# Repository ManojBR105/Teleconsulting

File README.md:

# Teleconsulting
project demo video available at https://drive.google.com/file/d/1hCcPtmlnuc-eiRi7AZsOfsH53jTqFW1P/view?usp=sharing

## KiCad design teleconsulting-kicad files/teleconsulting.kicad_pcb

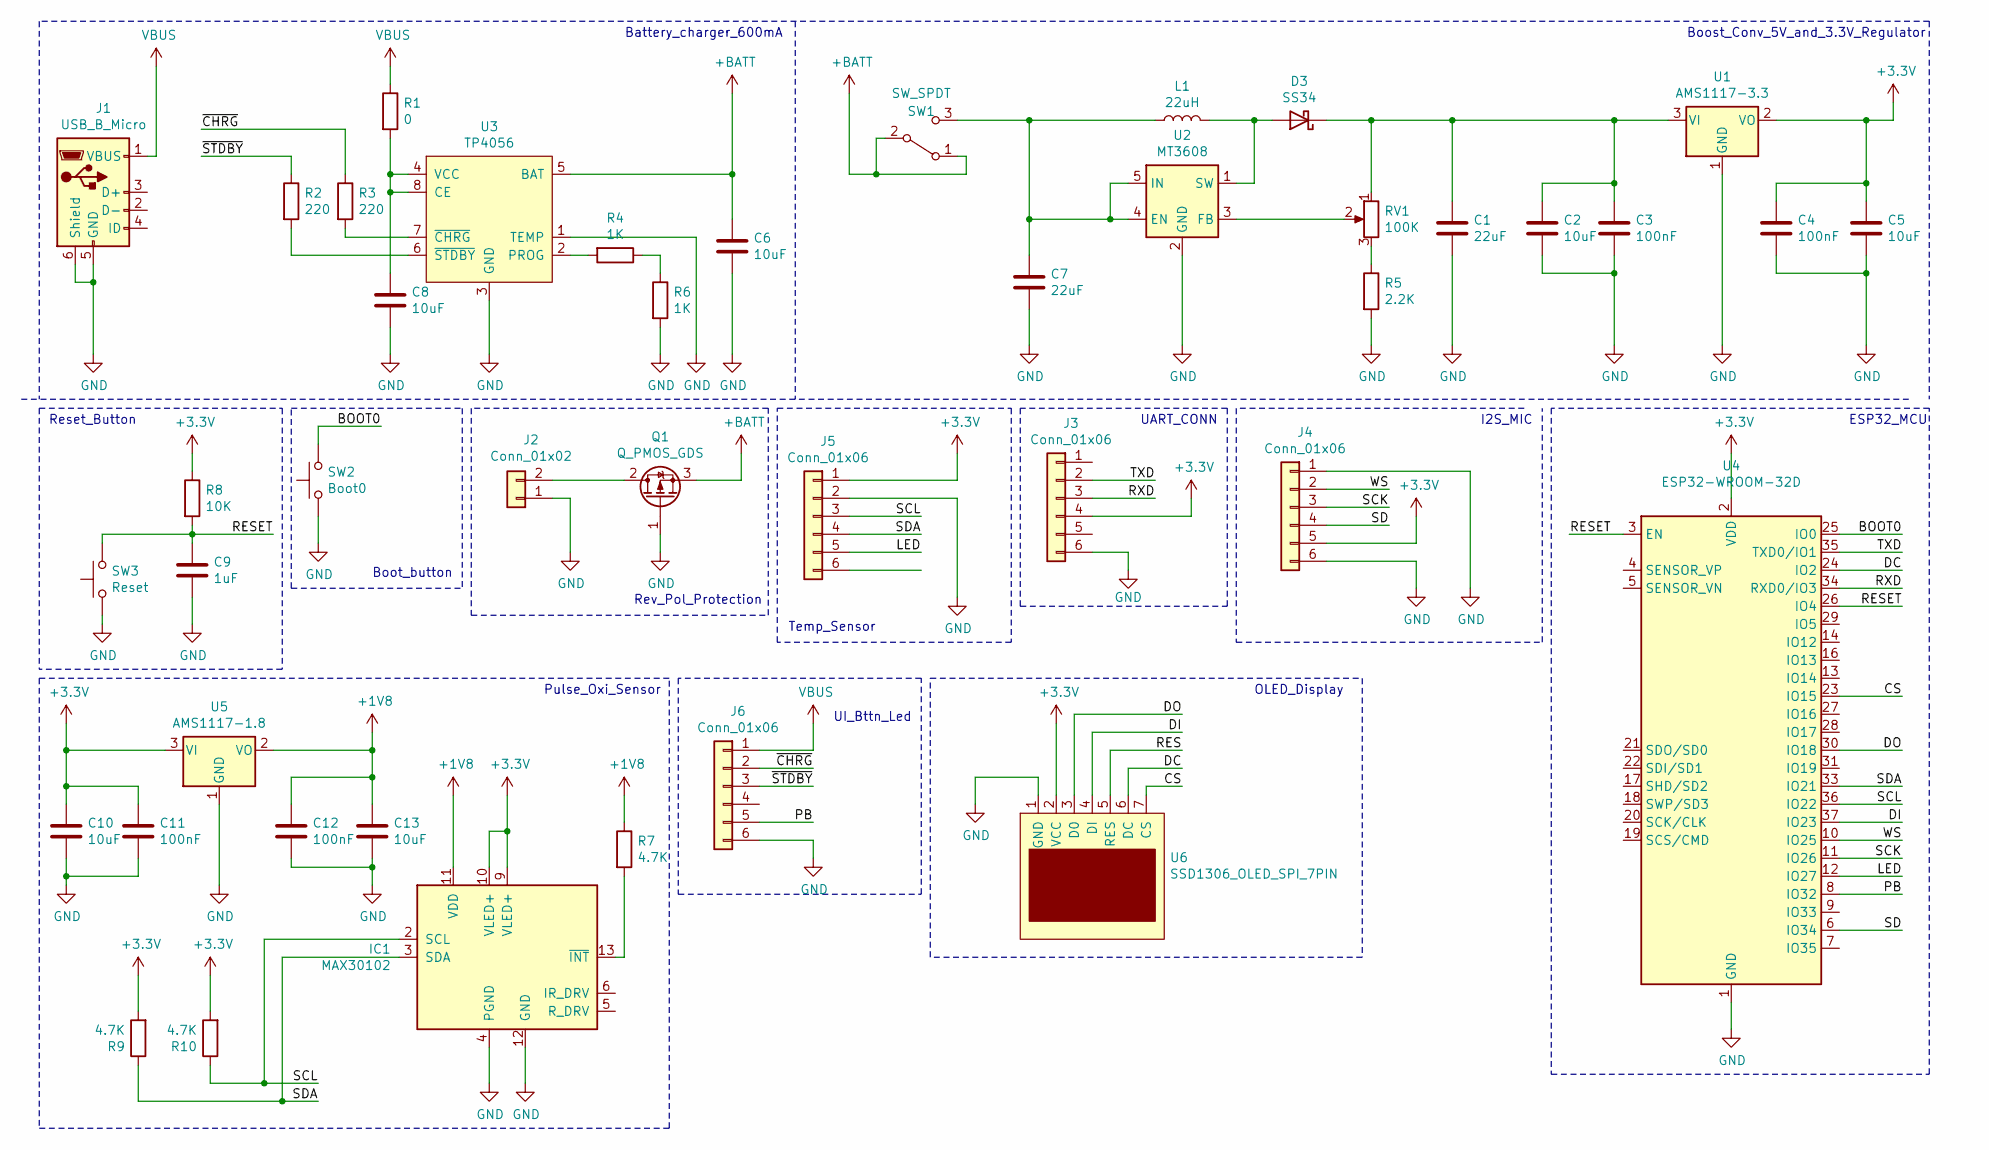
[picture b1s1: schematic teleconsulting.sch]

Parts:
C1, C7: 22uF; C_0805_2012Metric_Pad1.15x1.40mm_HandSolder
C2, C5, C10, C13: 10uF; C_0603_1608Metric_Pad1.05x0.95mm_HandSolder
C3, C4, C11, C12: 100nF; C_0603_1608Metric_Pad1.05x0.95mm_HandSolder
C6, C8: 10uF; C_0805_2012Metric_Pad1.15x1.40mm_HandSolder
C9: 1uF; C_0603_1608Metric_Pad1.05x0.95mm_HandSolder
D3: SS34; D_1812_4532Metric
IC1: MAX30102; Maxim_OLGA-14_3.3x5.6mm_P0.8mm
J1: USB_B_Micro; USB_Micro-B_Amphenol_10104110_Horizontal
J2: Conn_01x02; JST_EH_B2B-EH-A_1x02_P2.50mm_Vertical
J3, J4, J5, J6: Conn_01x06; JST_EH_B6B-EH-A_1x06_P2.50mm_Vertical
L1: 22uH; L_Taiyo-Yuden_NR-10050_9.8x10.0mm
Q1: Q_PMOS_GDS; SOT-23_Handsoldering
R1: 0; R_0805_2012Metric_Pad1.15x1.40mm_HandSolder
R2, R3: 220; R_0805_2012Metric_Pad1.15x1.40mm_HandSolder
R4, R6: 1K; R_0805_2012Metric_Pad1.15x1.40mm_HandSolder
R5: 2.2K; R_0603_1608Metric_Pad1.05x0.95mm_HandSolder
R7, R9, R10: 4.7K; R_0805_2012Metric_Pad1.15x1.40mm_HandSolder
R8: 10K; R_0603_1608Metric_Pad1.05x0.95mm_HandSolder
RV1: 100K; Potentiometer_Bourns_TC33X_Vertical
SW1: SW_SPDT; SW_CuK_OS102011MA1QN1_SPDT_Angled
SW2: Boot0; SW_Push_SPST_NO_Alps_SKRK
SW3: Reset; SW_Push_SPST_NO_Alps_SKRK
U1: AMS1117-3.3; SOT-223-3_TabPin2
U2: MT3608; SOT-23-6_Handsoldering
U3: TP4056; SOIC-8_3.9x4.9mm_P1.27mm
U4: ESP32-WROOM-32D; ESP32-WROOM-32
U5: AMS1117-1.8; SOT-223-3_TabPin2
U6: SSD1306_OLED_SPI_7PIN; ssd1306_oled_spi_7pin

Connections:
+1V8: C12.1, C13.1, IC1.11 (VDD), R7.1, U5.2 (VO)
+3V3: C4.1, C5.1, C10.1, C11.1, IC1.9 (VLED+), IC1.10 (VLED+), J3.4, J4.5, J5.1, R8.1, R9.2, R10.2, U1.2 (VO), U4.2 (VDD), U5.3 (VI), U6.2 (VCC)
+BATT: C6.1, Q1.3 (S), SW1.1 (A), SW1.2 (B), U3.5 (BAT)
/BOOT0: SW2.2, U4.25 (IO0)
/CS: U4.23 (IO15), U6.7 (CS)
/DC: U4.24 (IO2), U6.6 (DC)
/DI: U4.37 (IO23), U6.4 (DI)
/DO: U4.30 (IO18), U6.3 (D0)
/LED: J5.5, U4.12 (IO27)
/PB: J6.5, U4.8 (IO32)
/RESET: C9.1, R8.2, SW3.2, U4.3 (EN), U4.26 (IO4)
/RXD: J3.3, U4.34 (RXD0/IO3)
/SCK: J4.3, U4.11 (IO26)
/SCL: IC1.2 (SCL), J5.3, R10.1, U4.36 (IO22)
/SD: J4.4, U4.6 (IO34)
/SDA: IC1.3 (SDA), J5.4, R9.1, U4.33 (IO21)
/TXD: J3.2, U4.35 (TXD0/IO1)
/WS: J4.2, U4.10 (IO25)
/~CHRG: J6.2, R3.1
/~STDBY: J6.3, R2.1
GND: C1.2, C2.2, C3.2, C4.2, C5.2, C6.2, C7.2, C8.2, C9.2, C10.2, C11.2, C12.2, C13.2, IC1.4 (PGND), IC1.12 (GND), J1.5 (GND), J1.6 (Shield), J2.1, J3.6, J4.1, J4.6, J5.2, J6.6, Q1.1 (G), R5.2, R6.2, SW2.1, SW3.1, U1.1 (GND), U2.2 (GND), U3.1 (TEMP), U3.3 (GND), U4.1 (GND), U4.15 (GND), U4.38 (GND), U4.39 (GND), U5.1 (GND), U6.1 (GND)
unnamed: C1.1, C2.1, C3.1, D3.1 (K), RV1.1, U1.3 (VI)
unnamed: C7.1, L1.1, SW1.3 (C), U2.4 (EN), U2.5 (IN)
unnamed: C8.1, R1.2, U3.4 (VCC), U3.8 (CE)
unnamed: D3.2 (A), L1.2, U2.1 (SW)
unnamed: IC1.13 (~INT), R7.2
unnamed: J2.2, Q1.2 (D)
unnamed: R2.2, U3.6 (~STDBY)
unnamed: R3.2, U3.7 (~CHRG)
unnamed: R4.1, R6.1
unnamed: R4.2, U3.2 (PROG)
unnamed: R5.1, RV1.3
unnamed: RV1.2, U2.3 (FB)
VBUS: J1.1 (VBUS), J6.1, R1.1

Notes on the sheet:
Battery_charger_600mA
Boost_Conv_5V_and_3.3V_Regulator
Reset_Button
Rev_Pol_Protection
Boot_button
ESP32_MCU
Temp_Sensor
I2S_MIC
UART_CONN
Pulse_Oxi_Sensor
UI_Bttn_Led
OLED_Display

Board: 2 copper layers, 43 parts (9 on the bottom side), 34 nets, no tracks yet.

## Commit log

2021-04-04 This is a new commit for what I originally planned to be amended
2021-04-04 aster
2021-04-04 final prortotype
2021-04-04 doctor
2021-04-04 doctor rename
2021-04-05 Doctor App completed
2021-04-06 fixed temperature sensor issue
2021-04-21 fixed few bugs related to startup
2021-05-12 pcb files
2021-06-14 BP added
2021-06-19 final revision for Faer
2022-07-04 Major updates, compaitable with new device, ML classifier, individual parameter recording, recent versions libraries updated
